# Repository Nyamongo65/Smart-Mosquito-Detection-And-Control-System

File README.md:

# Smart-Mosquito-Detection-And-Control-System

## Colaborators
1. Masika - Supervisor

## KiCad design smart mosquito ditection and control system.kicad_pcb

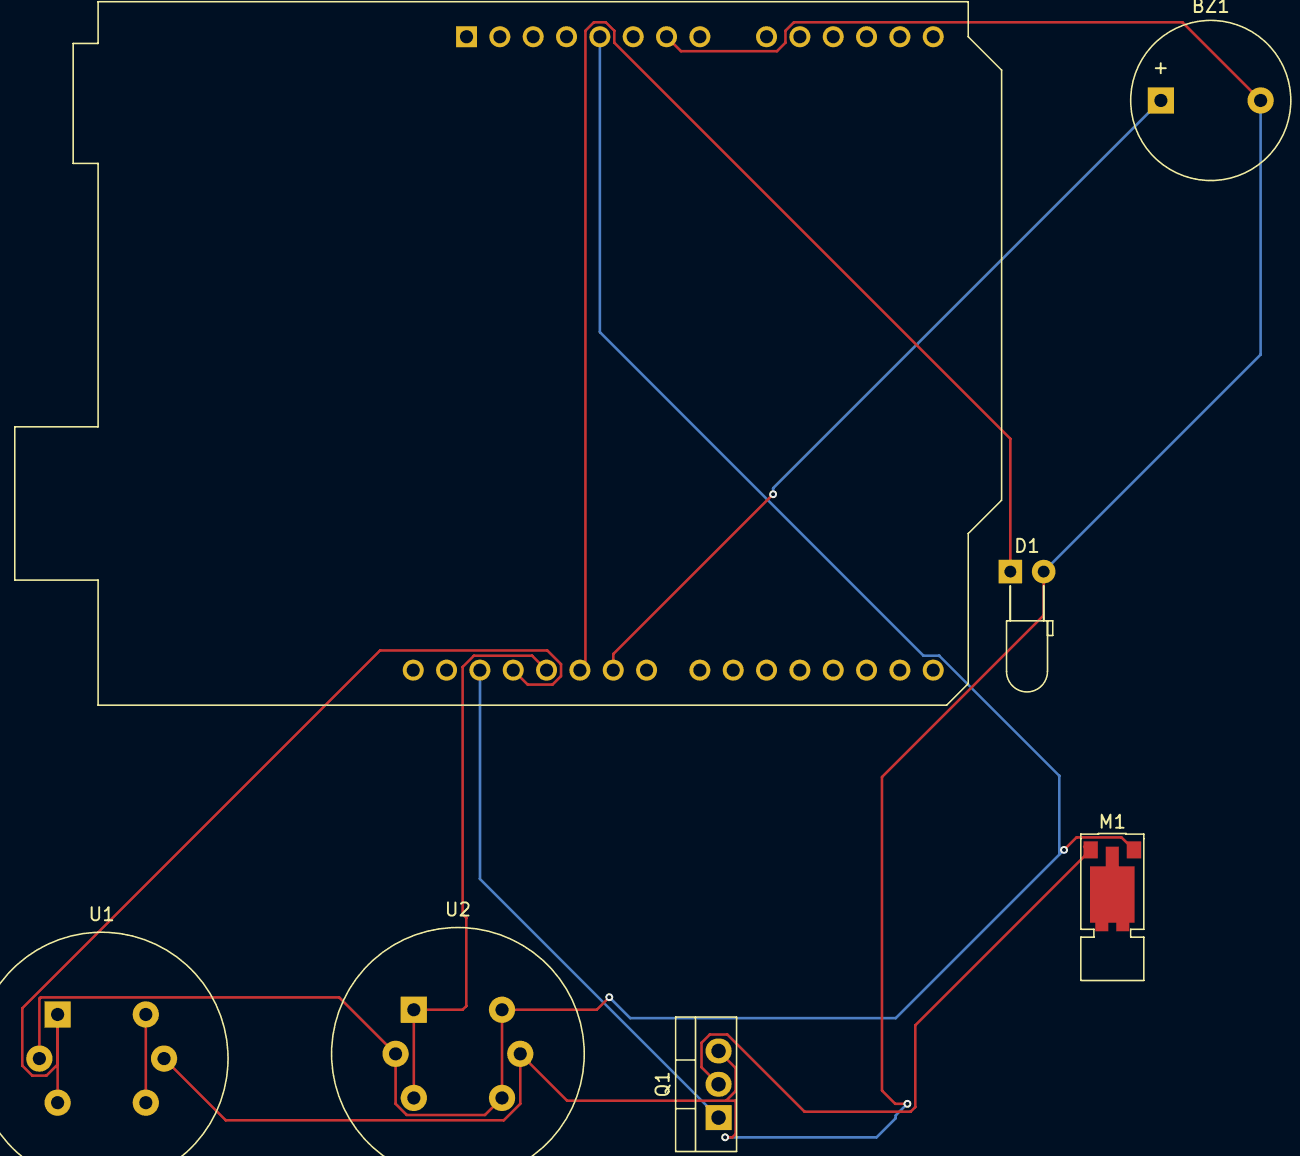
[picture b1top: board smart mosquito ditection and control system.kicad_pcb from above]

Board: 2 copper layers, 7 parts (0 on the bottom side), 9 nets.

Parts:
A1: Arduino_UNO_R2
BZ1: Buzzer; Buzzer_12x9.5RM7.6
D1: LED; LED_D3.0mm_Horizontal_O3.81mm_Z2.0mm
M1: Motor_DC; Vybronics_VZ30C1T8219732L
Q1: IRLZ34N; TO-220-3_Vertical
U1, U2: MQ-6

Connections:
unnamed: A1.5 (+5V), M1.2 (-), U1.2 (VH+), U2.2 (VH+), U2.4 (A2), U2.6 (A1)
unnamed: A1.24 (D9), BZ1.1 (+)
unnamed: A1.25 (D10), D1.1 (K)
unnamed: A1.26 (D11), U2.1 (B1), U2.3 (B2)
unnamed: A1.27 (D12), U1.1 (B1), U1.3 (B2)
unnamed: A1.28 (D13), Q1.1 (G)
unnamed: A1.7 (GND), BZ1.2 (-), D1.2 (A), Q1.3 (S), U1.5 (VH-), U2.5 (VH-)
unnamed: M1.1 (+), Q1.2 (D)
unnamed: U1.4 (A2), U1.6 (A1)
